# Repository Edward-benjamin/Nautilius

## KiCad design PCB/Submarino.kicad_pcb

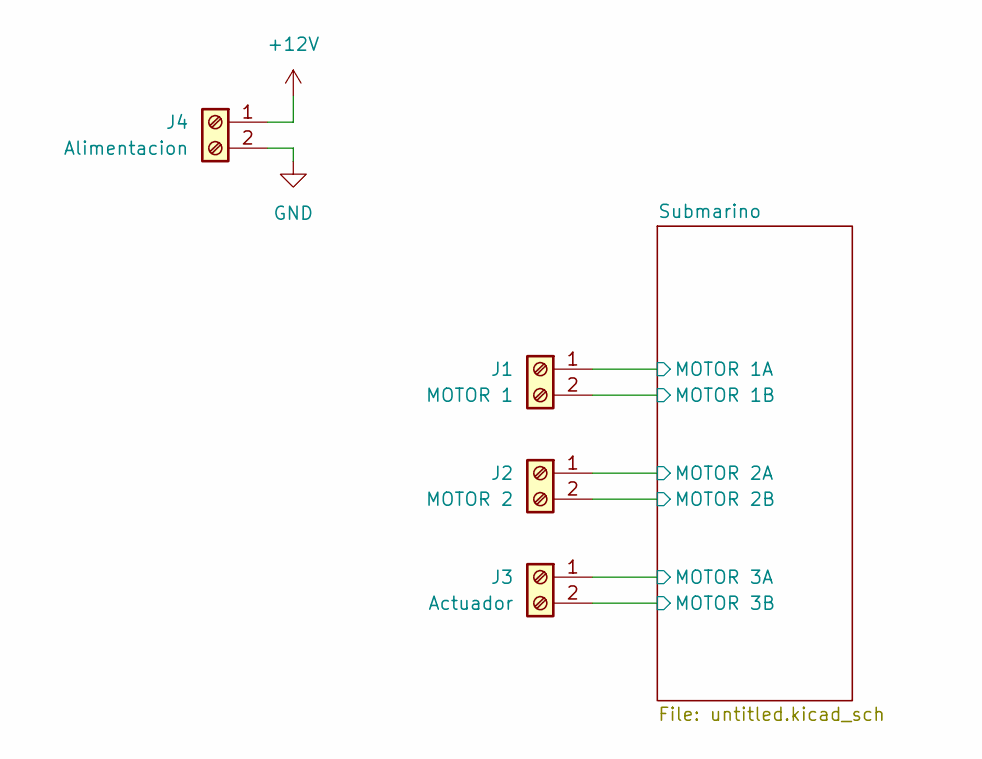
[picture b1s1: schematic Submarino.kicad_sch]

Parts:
J1: MOTOR 1; Molex_KK-254_AE-6410-02A_1x02_P2.54mm_Vertical
J2: MOTOR 2; Molex_KK-254_AE-6410-02A_1x02_P2.54mm_Vertical
J3: Actuador; Molex_KK-254_AE-6410-02A_1x02_P2.54mm_Vertical
J4: Alimentacion; Molex_KK-254_AE-6410-02A_1x02_P2.54mm_Vertical

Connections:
+12V: J4.1; also elsewhere on the board
/Submarino/MOTOR 1A: J1.1; also elsewhere on the board
/Submarino/MOTOR 1B: J1.2; also elsewhere on the board
/Submarino/MOTOR 2A: J2.1; also elsewhere on the board
/Submarino/MOTOR 2B: J2.2; also elsewhere on the board
/Submarino/MOTOR 3A: J3.1; also elsewhere on the board
/Submarino/MOTOR 3B: J3.2; also elsewhere on the board
GND: J4.2; also elsewhere on the board

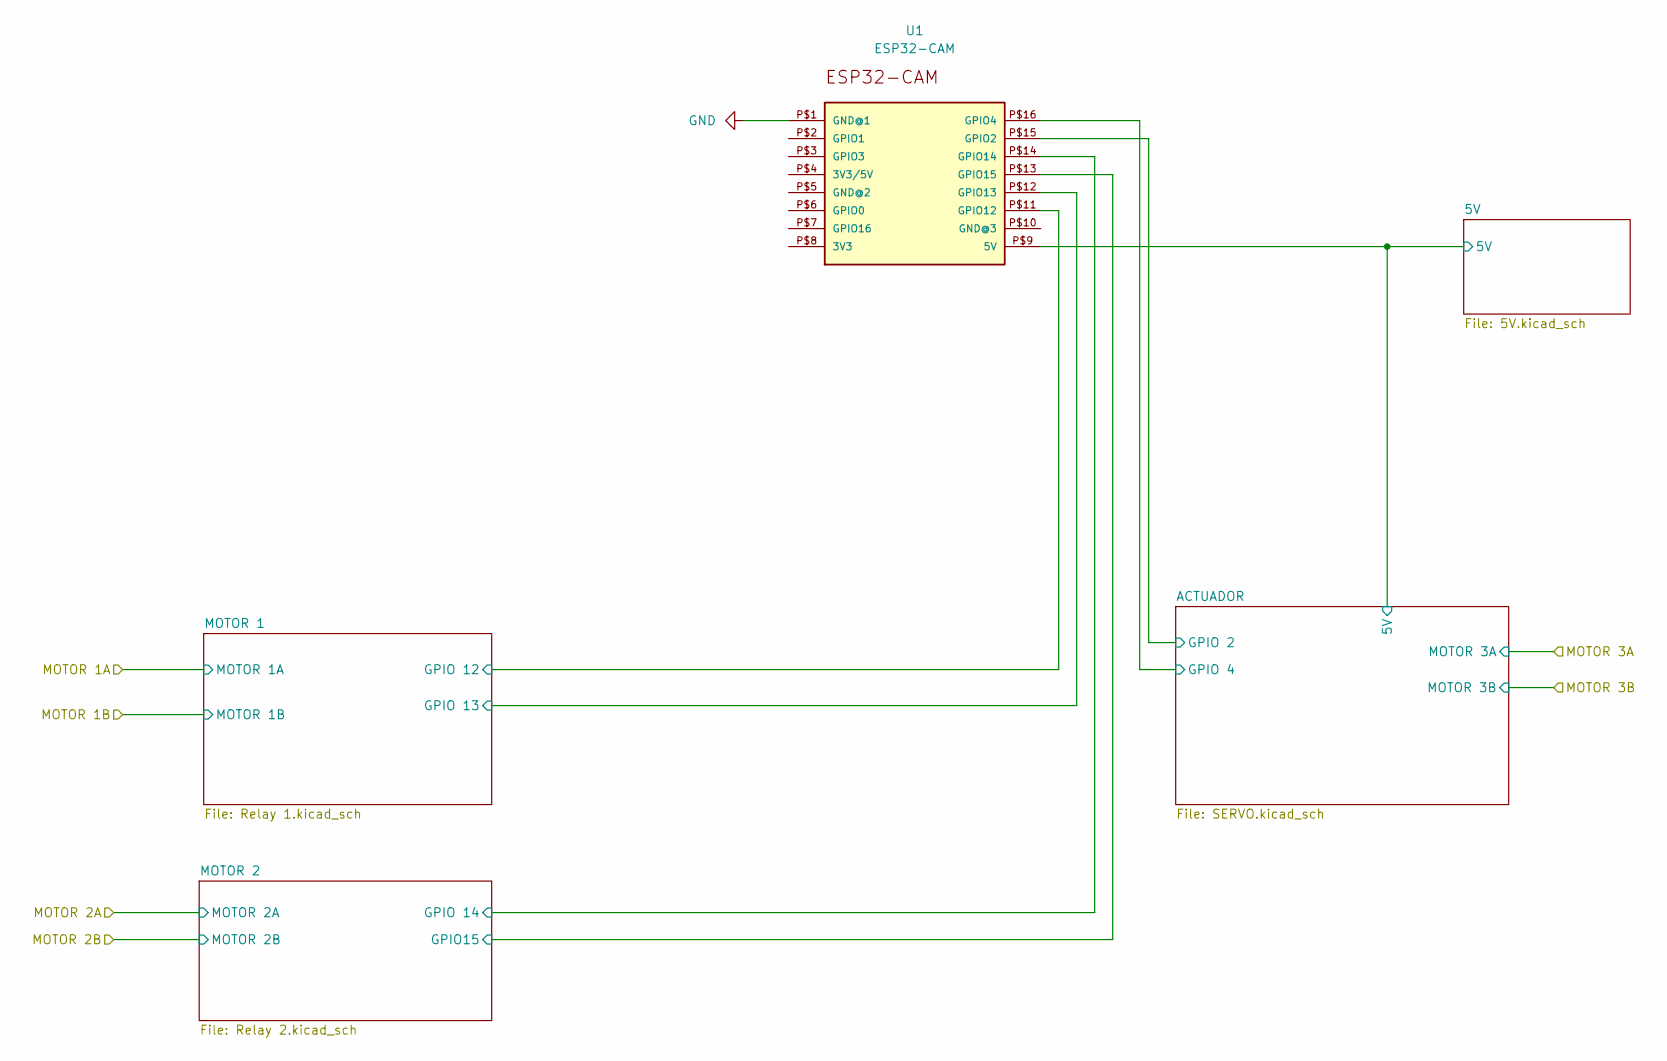
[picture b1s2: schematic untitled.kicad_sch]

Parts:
U1: ESP32-CAM

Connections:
/Submarino/5V/5V: U1.P$9 (5V); also elsewhere on the board
/Submarino/ACTUADOR/GPIO 2: U1.P$15 (GPIO2); also elsewhere on the board
/Submarino/ACTUADOR/GPIO 4: U1.P$16 (GPIO4); also elsewhere on the board
/Submarino/MOTOR 1/GPIO 12: U1.P$11 (GPIO12); also elsewhere on the board
/Submarino/MOTOR 1/GPIO 13: U1.P$12 (GPIO13); also elsewhere on the board
/Submarino/MOTOR 2/GPIO15: U1.P$13 (GPIO15); also elsewhere on the board
/Submarino/MOTOR 2/GPIO 14: U1.P$14 (GPIO14); also elsewhere on the board
GND: U1.P$1 (GND@1); also elsewhere on the board

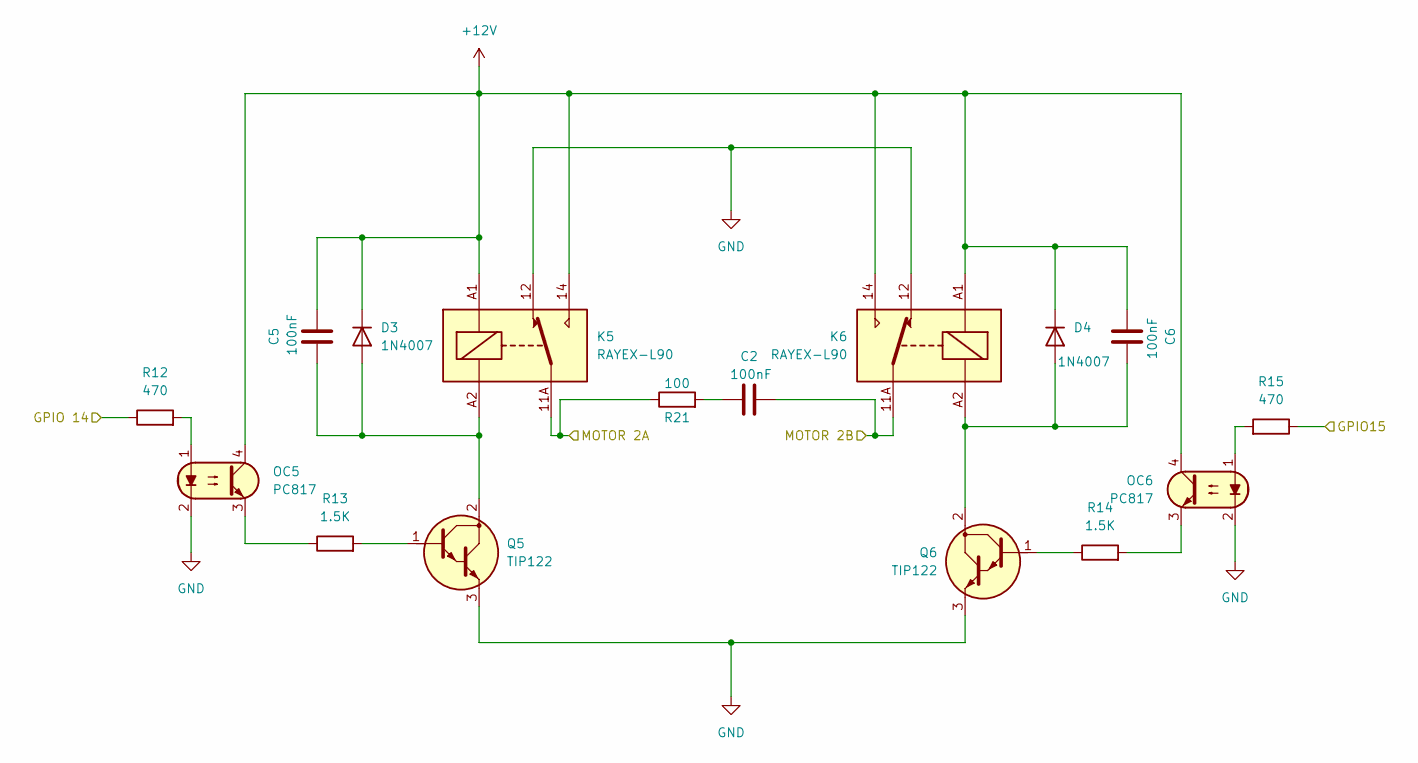
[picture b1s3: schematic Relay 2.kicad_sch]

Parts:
C2, C5, C6: 100nF; C_Disc_D4.3mm_W1.9mm_P5.00mm
D3, D4: 1N4007; D_DO-41_SOD81_P10.16mm_Horizontal
K5, K6: RAYEX-L90; Relay_SPDT_RAYEX-L90
OC5, OC6: PC817; DIP-4_W7.62mm_LongPads
Q5, Q6: TIP122; TO-220-3_Vertical_BCE
R12, R15: 470; R_Axial_DIN0207_L6.3mm_D2.5mm_P10.16mm_Horizontal
R13, R14: 1.5K; R_Axial_DIN0207_L6.3mm_D2.5mm_P10.16mm_Horizontal
R21: 100; R_Axial_DIN0207_L6.3mm_D2.5mm_P10.16mm_Horizontal

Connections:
+12V: C5.2, C6.1, D3.1 (K), D4.1 (K), K5.14, K5.A1, K6.14, K6.A1, OC5.4, OC6.4; also elsewhere on the board
/Submarino/MOTOR 2/GPIO15: R15.1; also elsewhere on the board
/Submarino/MOTOR 2/GPIO 14: R12.1; also elsewhere on the board
/Submarino/MOTOR 2A: K5.11A, K5.11B, R21.1; also elsewhere on the board
/Submarino/MOTOR 2B: C2.2, K6.11A, K6.11B; also elsewhere on the board
GND: K5.12, K6.12, OC5.2, OC6.2, Q5.3 (E), Q6.3 (E); also elsewhere on the board
unnamed: C2.1, R21.2
unnamed: C5.1, D3.2 (A), K5.A2, Q5.2 (C)
unnamed: C6.2, D4.2 (A), K6.A2, Q6.2 (C)
unnamed: OC5.1, R12.2
unnamed: OC5.3, R13.1
unnamed: OC6.1, R15.2
unnamed: OC6.3, R14.2
unnamed: Q5.1 (B), R13.2
unnamed: Q6.1 (B), R14.1

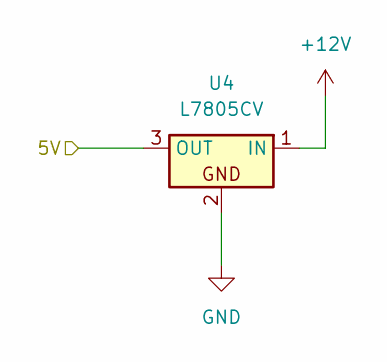
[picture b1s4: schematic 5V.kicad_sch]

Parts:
U4: L7805CV; TO-220-3_Vertical

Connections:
+12V: U4.1 (IN); also elsewhere on the board
/Submarino/5V/5V: U4.3 (OUT); also elsewhere on the board
GND: U4.2; also elsewhere on the board

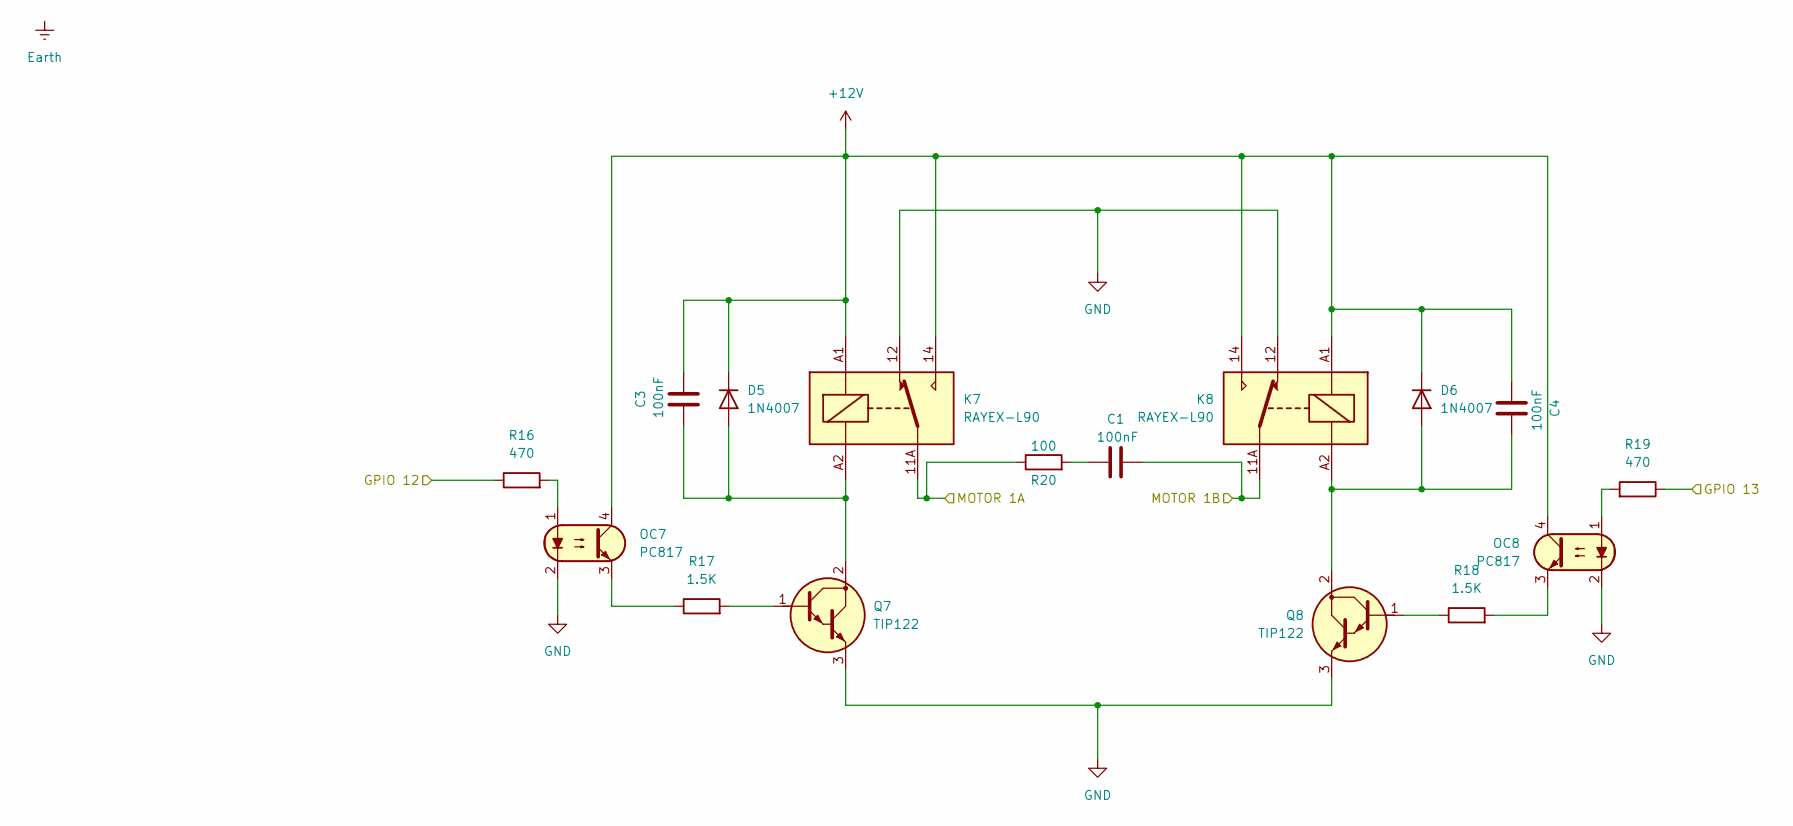
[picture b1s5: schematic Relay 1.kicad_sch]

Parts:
C1, C3, C4: 100nF; C_Disc_D4.3mm_W1.9mm_P5.00mm
D5, D6: 1N4007; D_DO-41_SOD81_P10.16mm_Horizontal
K7, K8: RAYEX-L90; Relay_SPDT_RAYEX-L90
OC7, OC8: PC817; DIP-4_W7.62mm_LongPads
Q7, Q8: TIP122; TO-220-3_Vertical_BCE
R16, R19: 470; R_Axial_DIN0207_L6.3mm_D2.5mm_P10.16mm_Horizontal
R17, R18: 1.5K; R_Axial_DIN0207_L6.3mm_D2.5mm_P10.16mm_Horizontal
R20: 100; R_Axial_DIN0207_L6.3mm_D2.5mm_P10.16mm_Horizontal

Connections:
+12V: C3.2, C4.1, D5.1 (K), D6.1 (K), K7.14, K7.A1, K8.14, K8.A1, OC7.4, OC8.4; also elsewhere on the board
/Submarino/MOTOR 1/GPIO 12: R16.1; also elsewhere on the board
/Submarino/MOTOR 1/GPIO 13: R19.1; also elsewhere on the board
/Submarino/MOTOR 1A: K7.11A, K7.11B, R20.1; also elsewhere on the board
/Submarino/MOTOR 1B: C1.2, K8.11A, K8.11B; also elsewhere on the board
GND: K7.12, K8.12, OC7.2, OC8.2, Q7.3 (E), Q8.3 (E); also elsewhere on the board
unnamed: C1.1, R20.2
unnamed: C3.1, D5.2 (A), K7.A2, Q7.2 (C)
unnamed: C4.2, D6.2 (A), K8.A2, Q8.2 (C)
unnamed: OC7.1, R16.2
unnamed: OC7.3, R17.1
unnamed: OC8.1, R19.2
unnamed: OC8.3, R18.2
unnamed: Q7.1 (B), R17.2
unnamed: Q8.1 (B), R18.1

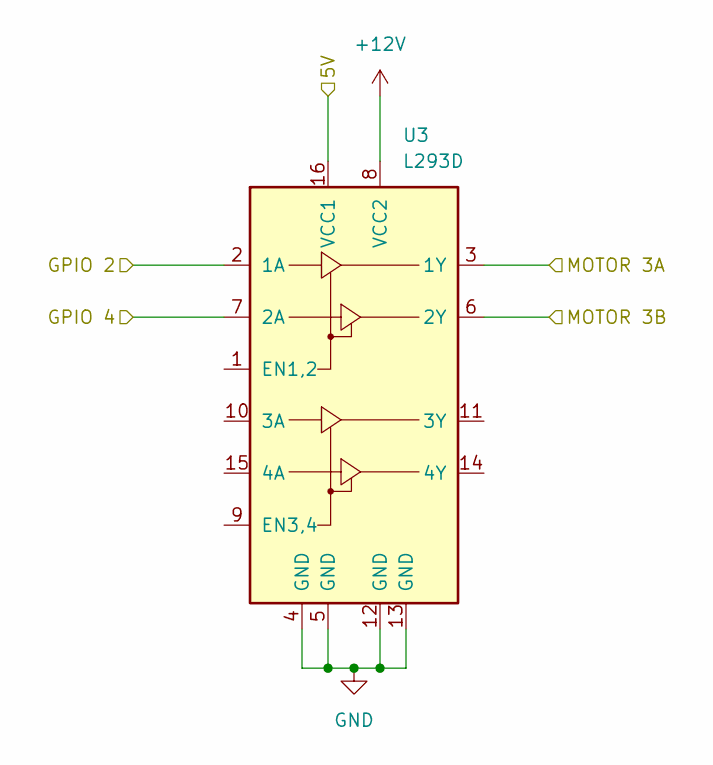
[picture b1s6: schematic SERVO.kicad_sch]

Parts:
U3: L293D; DIP-16_W7.62mm

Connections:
+12V: U3.8 (VCC2); also elsewhere on the board
/Submarino/5V/5V: U3.16 (VCC1); also elsewhere on the board
/Submarino/ACTUADOR/GPIO 2: U3.2 (1A); also elsewhere on the board
/Submarino/ACTUADOR/GPIO 4: U3.7 (2A); also elsewhere on the board
/Submarino/MOTOR 3A: U3.3 (1Y); also elsewhere on the board
/Submarino/MOTOR 3B: U3.6 (2Y); also elsewhere on the board
GND: U3.4 (GND), U3.5 (GND), U3.12 (GND), U3.13 (GND); also elsewhere on the board

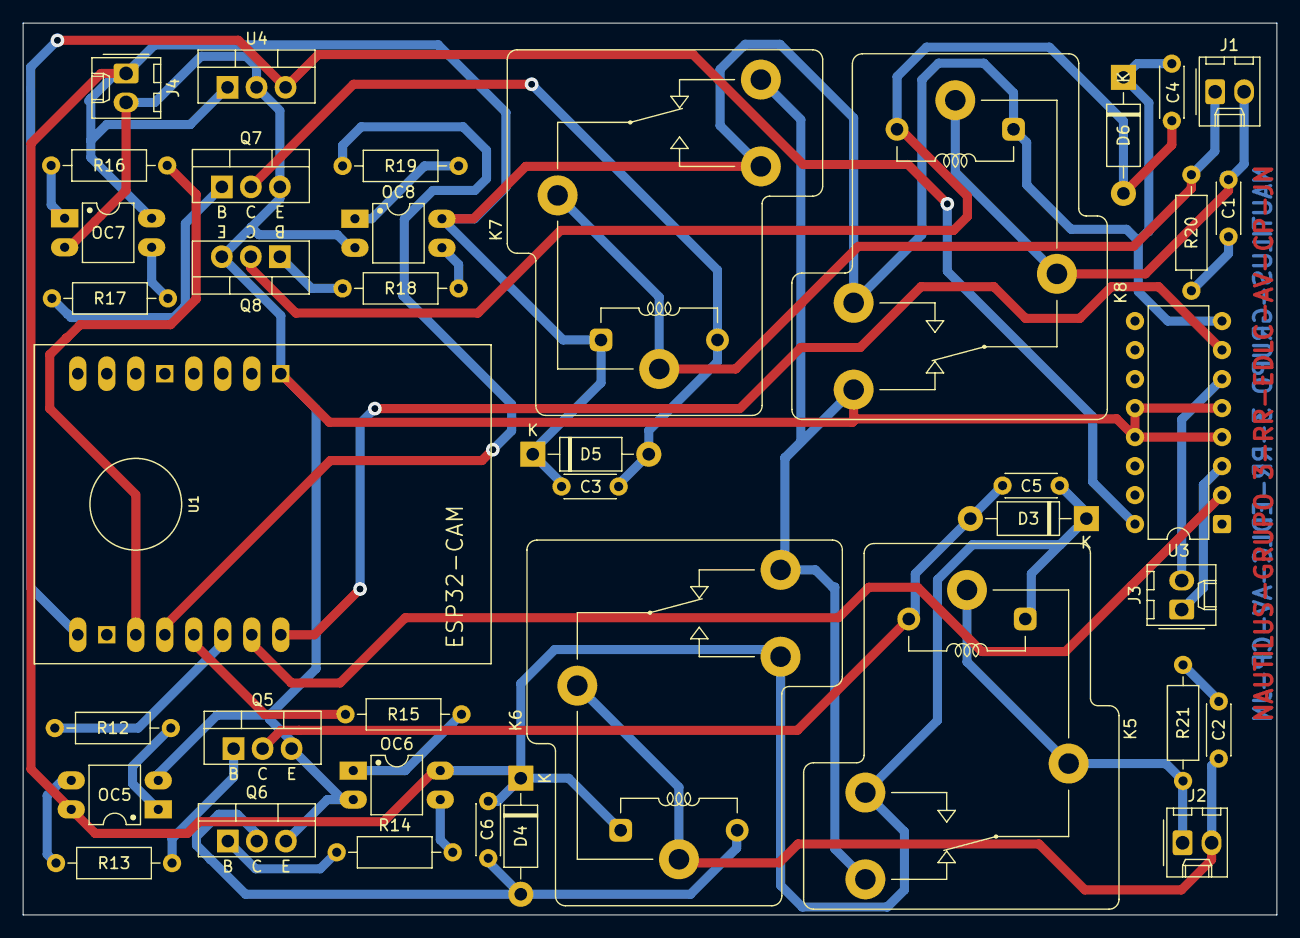
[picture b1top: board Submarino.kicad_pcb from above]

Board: 2 copper layers, 109.8 x 78.1 mm, 39 parts (0 on the bottom side), 33 nets.

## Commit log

2025-12-01 Create Diseño 3D
2025-12-01 Create hola
2025-12-01 Create solid
